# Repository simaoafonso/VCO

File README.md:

# VCO
VCO with triangle and wave shaper

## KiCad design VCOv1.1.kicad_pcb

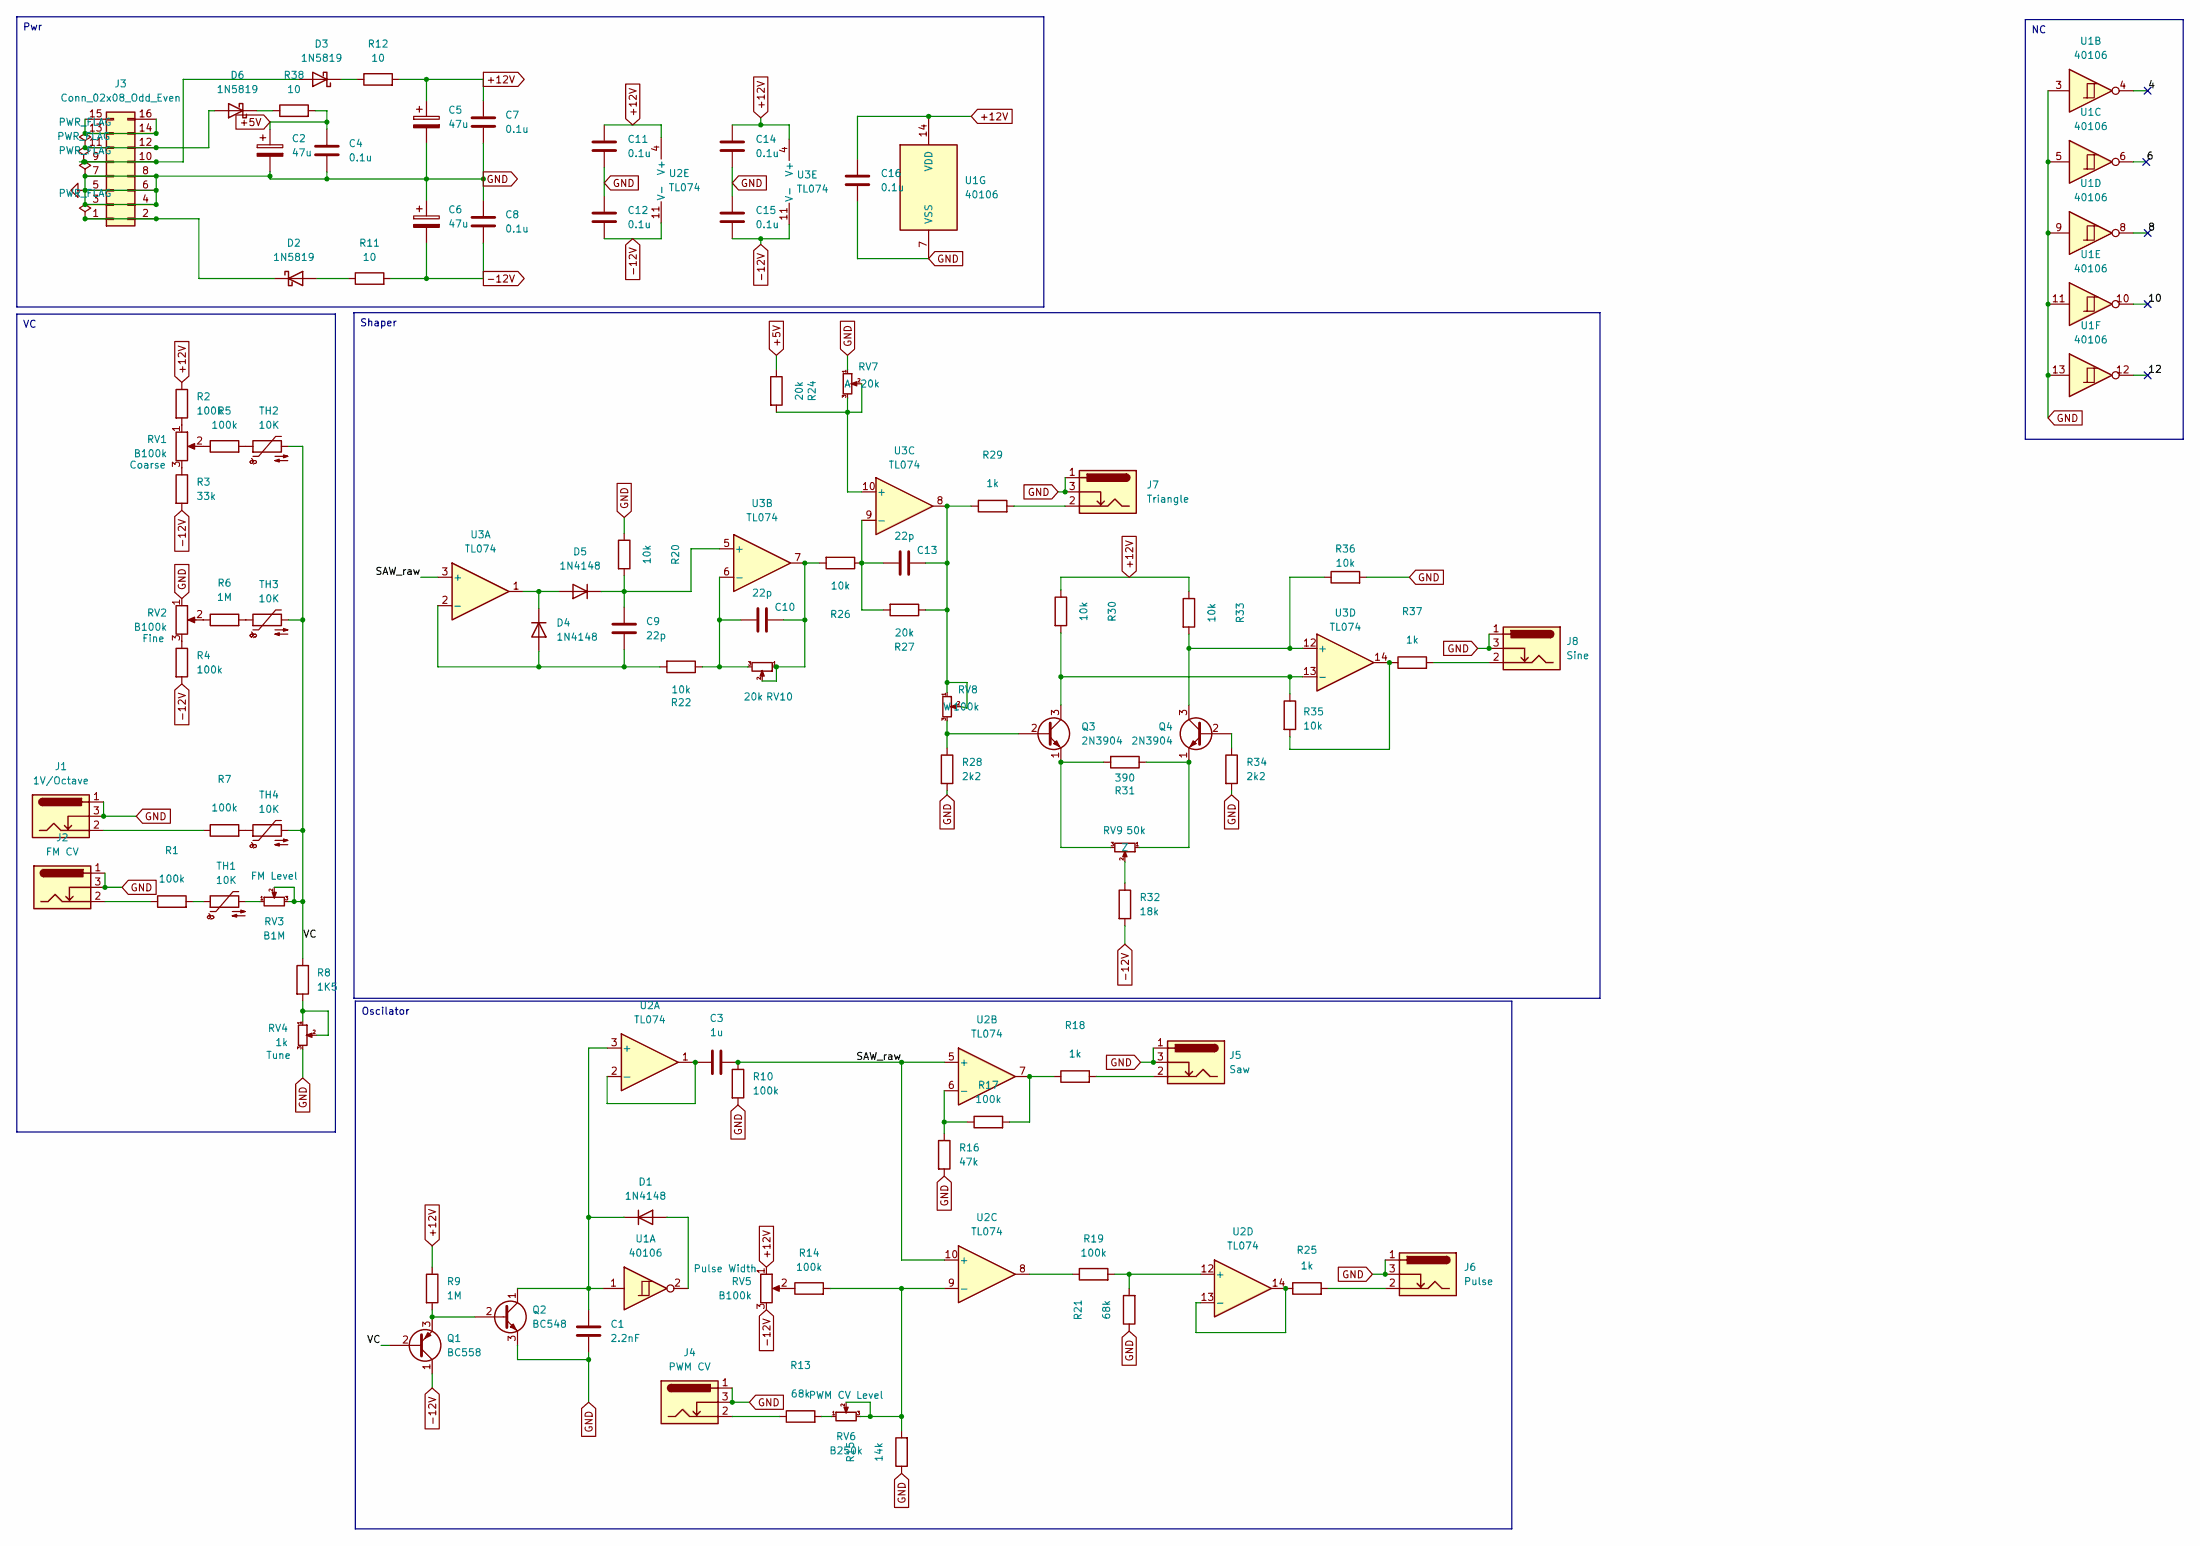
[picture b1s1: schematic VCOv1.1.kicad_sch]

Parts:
C1: 2.2nF; C_0805_2012Metric_Pad1.18x1.45mm_HandSolder
C2, C5, C6: 47u; CP_Radial_D4.0mm_P2.00mm
C3: 1u; C_0805_2012Metric_Pad1.18x1.45mm_HandSolder
C4, C7, C8, C11, C12, C14, C15, C16: 0.1u; C_0805_2012Metric_Pad1.18x1.45mm_HandSolder
C9, C10, C13: 22p; C_0805_2012Metric_Pad1.18x1.45mm_HandSolder
D1, D4, D5: 1N4148; D_SOD-123F
D2, D3, D6: 1N5819; D_DO-214AC_SMA
J1: 1V/Octave; MJ-3507
J2: FM CV; MJ-3507
J3: Conn_02x08_Odd_Even; IDC-Header_2x08_P2.54mm_Vertical
J4: PWM CV; MJ-3507
J5: Saw; MJ-3507
J6: Pulse; MJ-3507
J7: Triangle; MJ-3507
J8: Sine; MJ-3507
Q1: BC558; TO-92_Inline
Q2: BC548; TO-92_Inline
Q3, Q4: 2N3904; TO-92_Inline
R1, R2, R4, R5, R7, R10, R14, R17, R19: 100k; R_0805_2012Metric_Pad1.15x1.40mm_HandSolder
R3: 33k; R_0805_2012Metric_Pad1.15x1.40mm_HandSolder
R6, R9: 1M; R_0805_2012Metric_Pad1.15x1.40mm_HandSolder
R8: 1K5; R_0805_2012Metric_Pad1.15x1.40mm_HandSolder
R11, R12, R38: 10; R_0805_2012Metric_Pad1.15x1.40mm_HandSolder
R13, R21: 68k; R_0805_2012Metric_Pad1.15x1.40mm_HandSolder
R15: 14k; R_0805_2012Metric_Pad1.15x1.40mm_HandSolder
R16: 47k; R_0805_2012Metric_Pad1.15x1.40mm_HandSolder
R18, R25, R29, R37: 1k; R_0805_2012Metric_Pad1.15x1.40mm_HandSolder
R20, R22, R26, R30, R33, R35, R36: 10k; R_0805_2012Metric_Pad1.15x1.40mm_HandSolder
R24, R27: 20k; R_0805_2012Metric_Pad1.15x1.40mm_HandSolder
R28, R34: 2k2; R_0805_2012Metric_Pad1.15x1.40mm_HandSolder
R31: 390; R_0805_2012Metric_Pad1.15x1.40mm_HandSolder
R32: 18k; R_0805_2012Metric_Pad1.15x1.40mm_HandSolder
RV1, RV2, RV5: B100k; Potentiometer_Alps_RK09K_Single_Vertical
RV3: B1M; Potentiometer_Alps_RK09K_Single_Vertical
RV4: 1k; Potentiometer_Bourns_3224W_Vertical
RV6: B250k; Potentiometer_Alps_RK09K_Single_Vertical
RV7, RV10: 20k; Potentiometer_Bourns_3224W_Vertical
RV8: 100k; Potentiometer_Bourns_3224W_Vertical
RV9: 50k; Potentiometer_Bourns_3224W_Vertical
TH1, TH2, TH3, TH4: 10K; R_0805_2012Metric_Pad1.15x1.40mm_HandSolder
U1: 40106; SOIC-14_3.9x8.65mm_Pitch1.27mm
U2, U3: TL074; SOIC-14_3.9x8.65mm_Pitch1.27mm

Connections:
+5V: C2.1, C4.1, R24.1, R38.2
+12V: C5.1, C7.1, C11.1, C14.1, C16.1, R2.1, R9.1, R12.2, R30.1, R33.1, RV5.1, U1.14 (VDD), U2.4 (V+), U3.4 (V+)
-12V: C6.2, C8.2, C12.2, C15.2, Q1.1 (C), R3.2, R4.2, R11.2, R32.2, RV5.3, U2.11 (V-), U3.11 (V-)
/4: U1.4
/6: U1.6
/8: U1.8
/10: U1.10
/12: U1.12
GND: C1.2, C2.2, C4.2, C5.2, C6.1, C7.2, C8.1, C11.2, C12.1, C14.2, C15.1, C16.2, J1.1, J1.3, J2.1, J2.3, J3.3, J3.4, J3.5, J3.6, J3.7, J3.8, J4.1, J4.3, J5.1, J5.3, J6.1, J6.3, J7.1, J7.3, J8.1, J8.3, Q2.3 (E), R10.2, R15.1, R16.2, R20.1, R21.1, R28.2, R34.2, R36.2, RV2.1, RV4.3, RV7.1, U1.3, U1.5, U1.7 (VSS), U1.9, U1.11, U1.13; also elsewhere on the board
unnamed 9: C10.1, R26.2, RV10.1, RV10.2, U3.7; also elsewhere on the board
unnamed 10: C13.1, R27.1, R29.1, RV8.1, RV8.2, U3.8; also elsewhere on the board
unnamed: D1.2 (A), U1.2
unnamed: C1.1, D1.1 (K), Q2.1 (C), U1.1, U2.3 (+)
unnamed: D2.2 (A), R11.1
unnamed: D2.1 (K), J3.1, J3.2
unnamed: D3.2 (A), J3.9, J3.10
unnamed: D3.1 (K), R12.1
unnamed: C9.1, D4.2 (A), R22.2, U3.2 (-)
unnamed: D4.1 (K), D5.2 (A), U3.1
unnamed: C9.2, D5.1 (K), R20.2, U3.5 (+)
unnamed: D6.2 (A), J3.11, J3.12
unnamed: D6.1 (K), R38.1
unnamed: J1.2, R7.1
unnamed: J2.2, R1.1
unnamed: J3.13, J3.14, J3.15, J3.16
unnamed: J4.2, R13.1
unnamed: J5.2, R18.2
unnamed: J6.2, R25.2
unnamed: J7.2, R29.2
unnamed: J8.2, R37.2
unnamed: Q1.2 (B), R8.1, RV3.2, RV3.3, TH2.2, TH3.2, TH4.2
unnamed: Q1.3 (E), Q2.2 (B), R9.2
unnamed 32: Q3.2 (B), R28.1, RV8.3; also elsewhere on the board
unnamed: Q3.3 (C), R30.2, R35.1, U3.13 (-)
unnamed 34: Q3.1 (E), R31.2, RV9.3; also elsewhere on the board
unnamed: Q4.2 (B), R34.1
unnamed: Q4.3 (C), R33.2, R36.1, U3.12 (+)
unnamed 37: Q4.1 (E), R31.1, RV9.1; also elsewhere on the board
unnamed: R1.2, TH1.1
unnamed: R2.2, RV1.1
unnamed: R3.1, RV1.3
unnamed: R4.1, RV2.3
unnamed: R5.1, RV1.2
unnamed: R5.2, TH2.1
unnamed: R6.1, RV2.2
unnamed: R6.2, TH3.1
unnamed: R7.2, TH4.1
unnamed 47: R8.2, RV4.1, RV4.2; also elsewhere on the board
unnamed: R13.2, RV6.1
unnamed: R14.1, RV5.2
unnamed: R17.2, R18.1, U2.7
unnamed: R19.1, U2.8
unnamed 52: R32.1, RV9.2; also elsewhere on the board
unnamed: R35.2, R37.1, U3.14
unnamed: RV3.1, TH1.2
unnamed: C3.1, U2.1, U2.2 (-)
unnamed: C3.2, R10.1, U2.5 (+), U2.10 (+), U3.3 (+)
unnamed: R16.1, R17.1, U2.6 (-)
unnamed: R14.2, R15.2, RV6.2, RV6.3, U2.9 (-)
unnamed: R19.2, R21.2, U2.12 (+)
unnamed: R25.1, U2.13 (-), U2.14
unnamed 61: C10.2, R22.1, RV10.3, U3.6 (-); also elsewhere on the board
unnamed 62: R24.2, RV7.2, RV7.3, U3.10 (+); also elsewhere on the board
unnamed: C13.2, R26.1, R27.2, U3.9 (-)

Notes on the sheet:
Oscilator
Shaper
Pwr

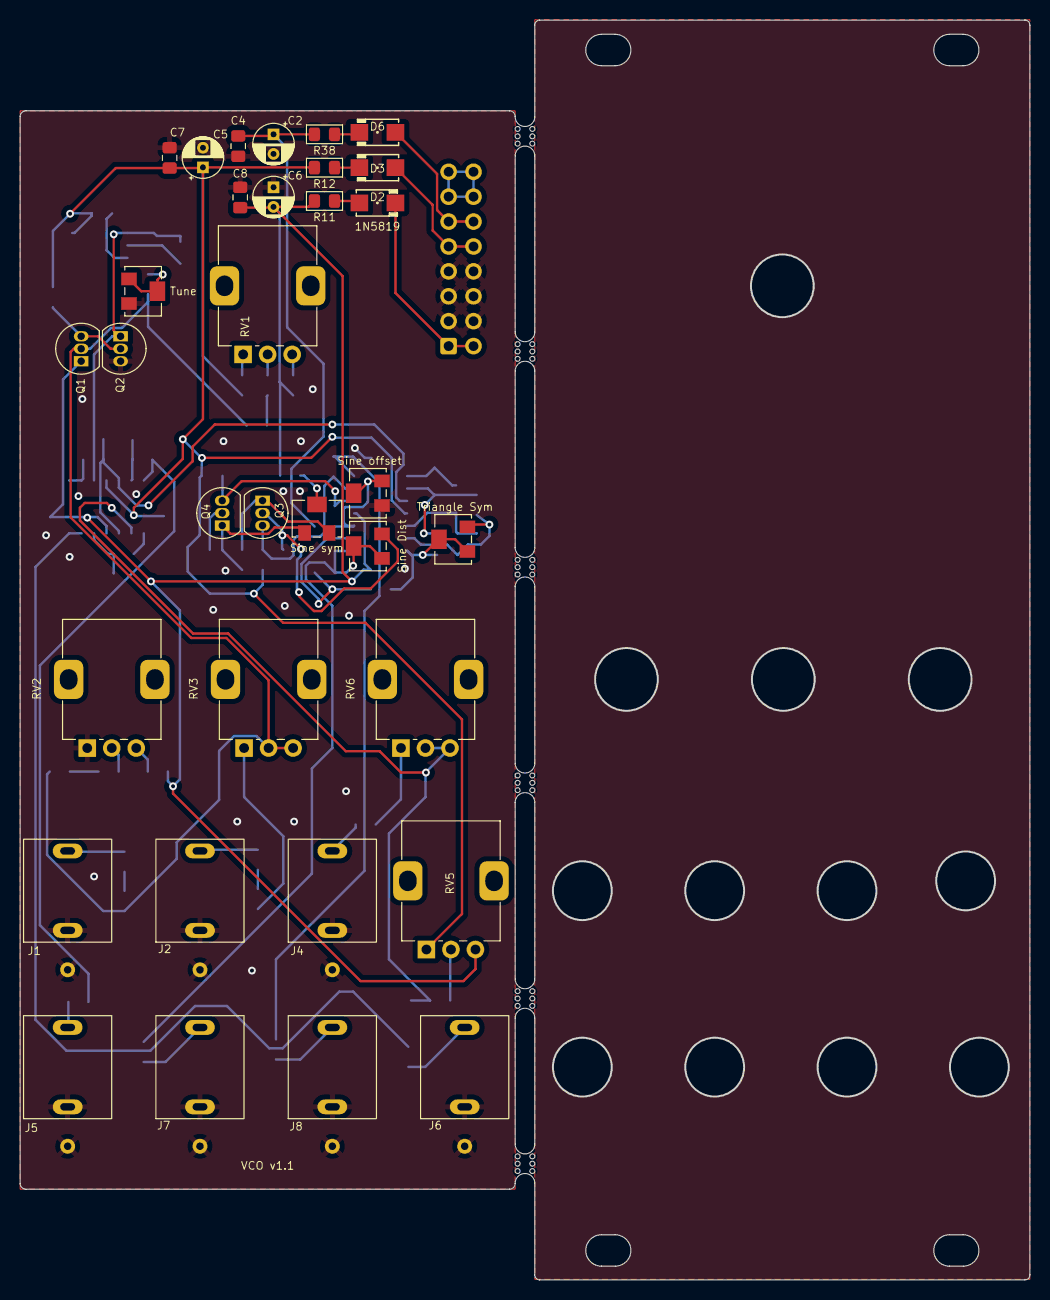
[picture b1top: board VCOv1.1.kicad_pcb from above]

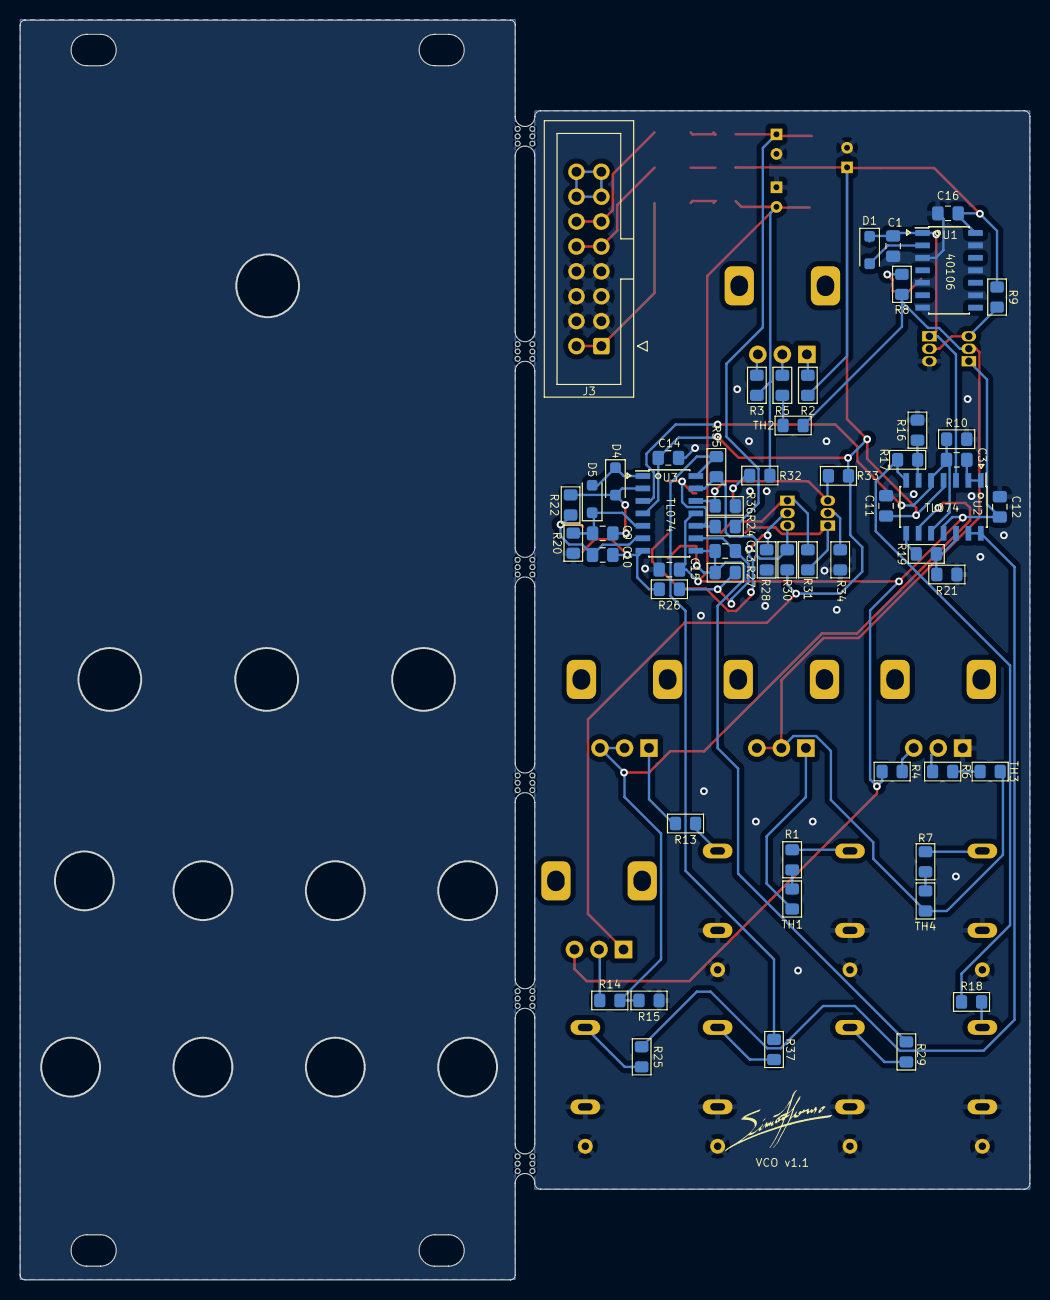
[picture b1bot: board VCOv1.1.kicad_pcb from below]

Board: 2 copper layers, 102.9 x 128.4 mm, 95 parts (56 on the bottom side), 59 nets.

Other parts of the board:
Sine Dist: 100k; Potentiometer_Bourns_3224W_Vertical
Sine offset: 20k; Potentiometer_Bourns_3224W_Vertical
Sine sym: 50k; Potentiometer_Bourns_3224W_Vertical
Triangle Sym: 20k; Potentiometer_Bourns_3224W_Vertical
Tune: 1k; Potentiometer_Bourns_3224W_Vertical
VCO v1.1: LOGO
mouse-bite-2mm-slot, mouse-bite-2mm-slot1, mouse-bite-2mm-slot2, mouse-bite-2mm-slot3, mouse-bite-2mm-slot4, mouse-bite-2mm-slot#2: VAL**; mouse-bite-2mm-slot

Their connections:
GND: Sine offset.1, Tune.3; also elsewhere on the board
unnamed 9: Triangle Sym.1, Triangle Sym.2; also elsewhere on the board
unnamed 10: Sine Dist.1, Sine Dist.2; also elsewhere on the board
unnamed 32: Sine Dist.3; also elsewhere on the board
unnamed 34: Sine sym.3; also elsewhere on the board
unnamed 37: Sine sym.1; also elsewhere on the board
unnamed 47: Tune.1, Tune.2; also elsewhere on the board
unnamed 52: Sine sym.2; also elsewhere on the board
unnamed 61: Triangle Sym.3; also elsewhere on the board
unnamed 62: Sine offset.2, Sine offset.3; also elsewhere on the board

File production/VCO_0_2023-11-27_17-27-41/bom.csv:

Designator,Footprint,Quantity,Value,LCSC Part #
C1,0805,1,2.2nF,
"C10, C13, C9",0805,3,22p,
"C11, C12, C14, C15, C16, C4, C7, C8",0805,8,0.1u,
"C2, C5, C6",CP_Radial_D4.0mm_P2.00mm,3,47u,
C3,0805,1,1u,
"D1, D4, D5",D_SOD-123F,3,1N4148,
"D2, D3, D6",D_DO-214AC_SMA,3,1N5819,
J1,MJ-3507,1,1V/Octave,
J2,MJ-3507,1,FM CV,
J3,IDC-Header_2x08_P2.54mm_Vertical,1,Conn_02x08_Odd_Even,
J4,MJ-3507,1,PWM CV,
J5,MJ-3507,1,Saw,
J6,MJ-3507,1,Pulse,
J7,MJ-3507,1,Triangle,
J8,MJ-3507,1,Sine,
Q1,TO-92_Inline,1,BC558,
Q2,TO-92_Inline,1,BC548,
"Q3, Q4",TO-92_Inline,2,2N3904,
"R1, R10, R14, R17, R19, R2, R4, R5, R7",0805,9,100k,
"R11, R12, R38",0805,3,10,
"R13, R21",0805,2,68k,
R15,0805,1,14k,
R16,0805,1,47k,
"R18, R25, R29, R37",0805,4,1k,
"R20, R22, R26, R30, R33, R35, R36, TH1, TH2, TH3, TH4",0805,11,10k,
"R24, R27",0805,2,20k,
"R28, R34",0805,2,2k2,
R3,0805,1,33k,
R31,0805,1,390,
R32,0805,1,18k,
"R6, R9",0805,2,1M,
R8,0805,1,1K5,
"RV1, RV2, RV5",Potentiometer_Alps_RK09K_Single_Vertical,3,B100k,
RV3,Potentiometer_Alps_RK09K_Single_Vertical,1,B1M,
RV6,Potentiometer_Alps_RK09K_Single_Vertical,1,B250k,
Sine Dist,Potentiometer_Bourns_3224W_Vertical,1,100k,
"Sine offset, Triangle Sym",Potentiometer_Bourns_3224W_Vertical,2,20k,
Sine sym,Potentiometer_Bourns_3224W_Vertical,1,50k,
Tune,Potentiometer_Bourns_3224W_Vertical,1,1k,
U1,SOIC-14_3.9x8.65mm_Pitch1.27mm,1,40106,
"U2, U3",SOIC-14_3.9x8.65mm_Pitch1.27mm,2,TL074,
"mouse-bite-2mm-slot_2, mouse-bite-2mm-slot, mouse-bite-2mm-slot1, mouse-bite-2mm-slot2, mouse-bite-2mm-slot3, mouse-bite-2mm-slot4",mouse-bite-2mm-slot,6,VAL**,
